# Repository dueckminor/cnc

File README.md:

# CNC-Mill

This is my first try to build a CNC-Mill

As a controller I use an ESP-32 with
[FluidNC](https://github.com/bdring/FluidNC)

I designed a PCB with the following features:
- 4 stepper motors (for the X1,X2,Y,Z axes)
- 1 spindle output (enable+pwm)
- 5 additional output pins
- 8 limit switches (5V powered), 2 for each axis
- 1 probe switch
- 3 additional input pins
- 1 SD-Card
- 1 I2C (for an OLED display)

This board gets connected using a 2x25 pin header to a connector-board
with many JST-XH connectors. This board contians also pull-up resistors
for each input switch (all inputs are active-low)

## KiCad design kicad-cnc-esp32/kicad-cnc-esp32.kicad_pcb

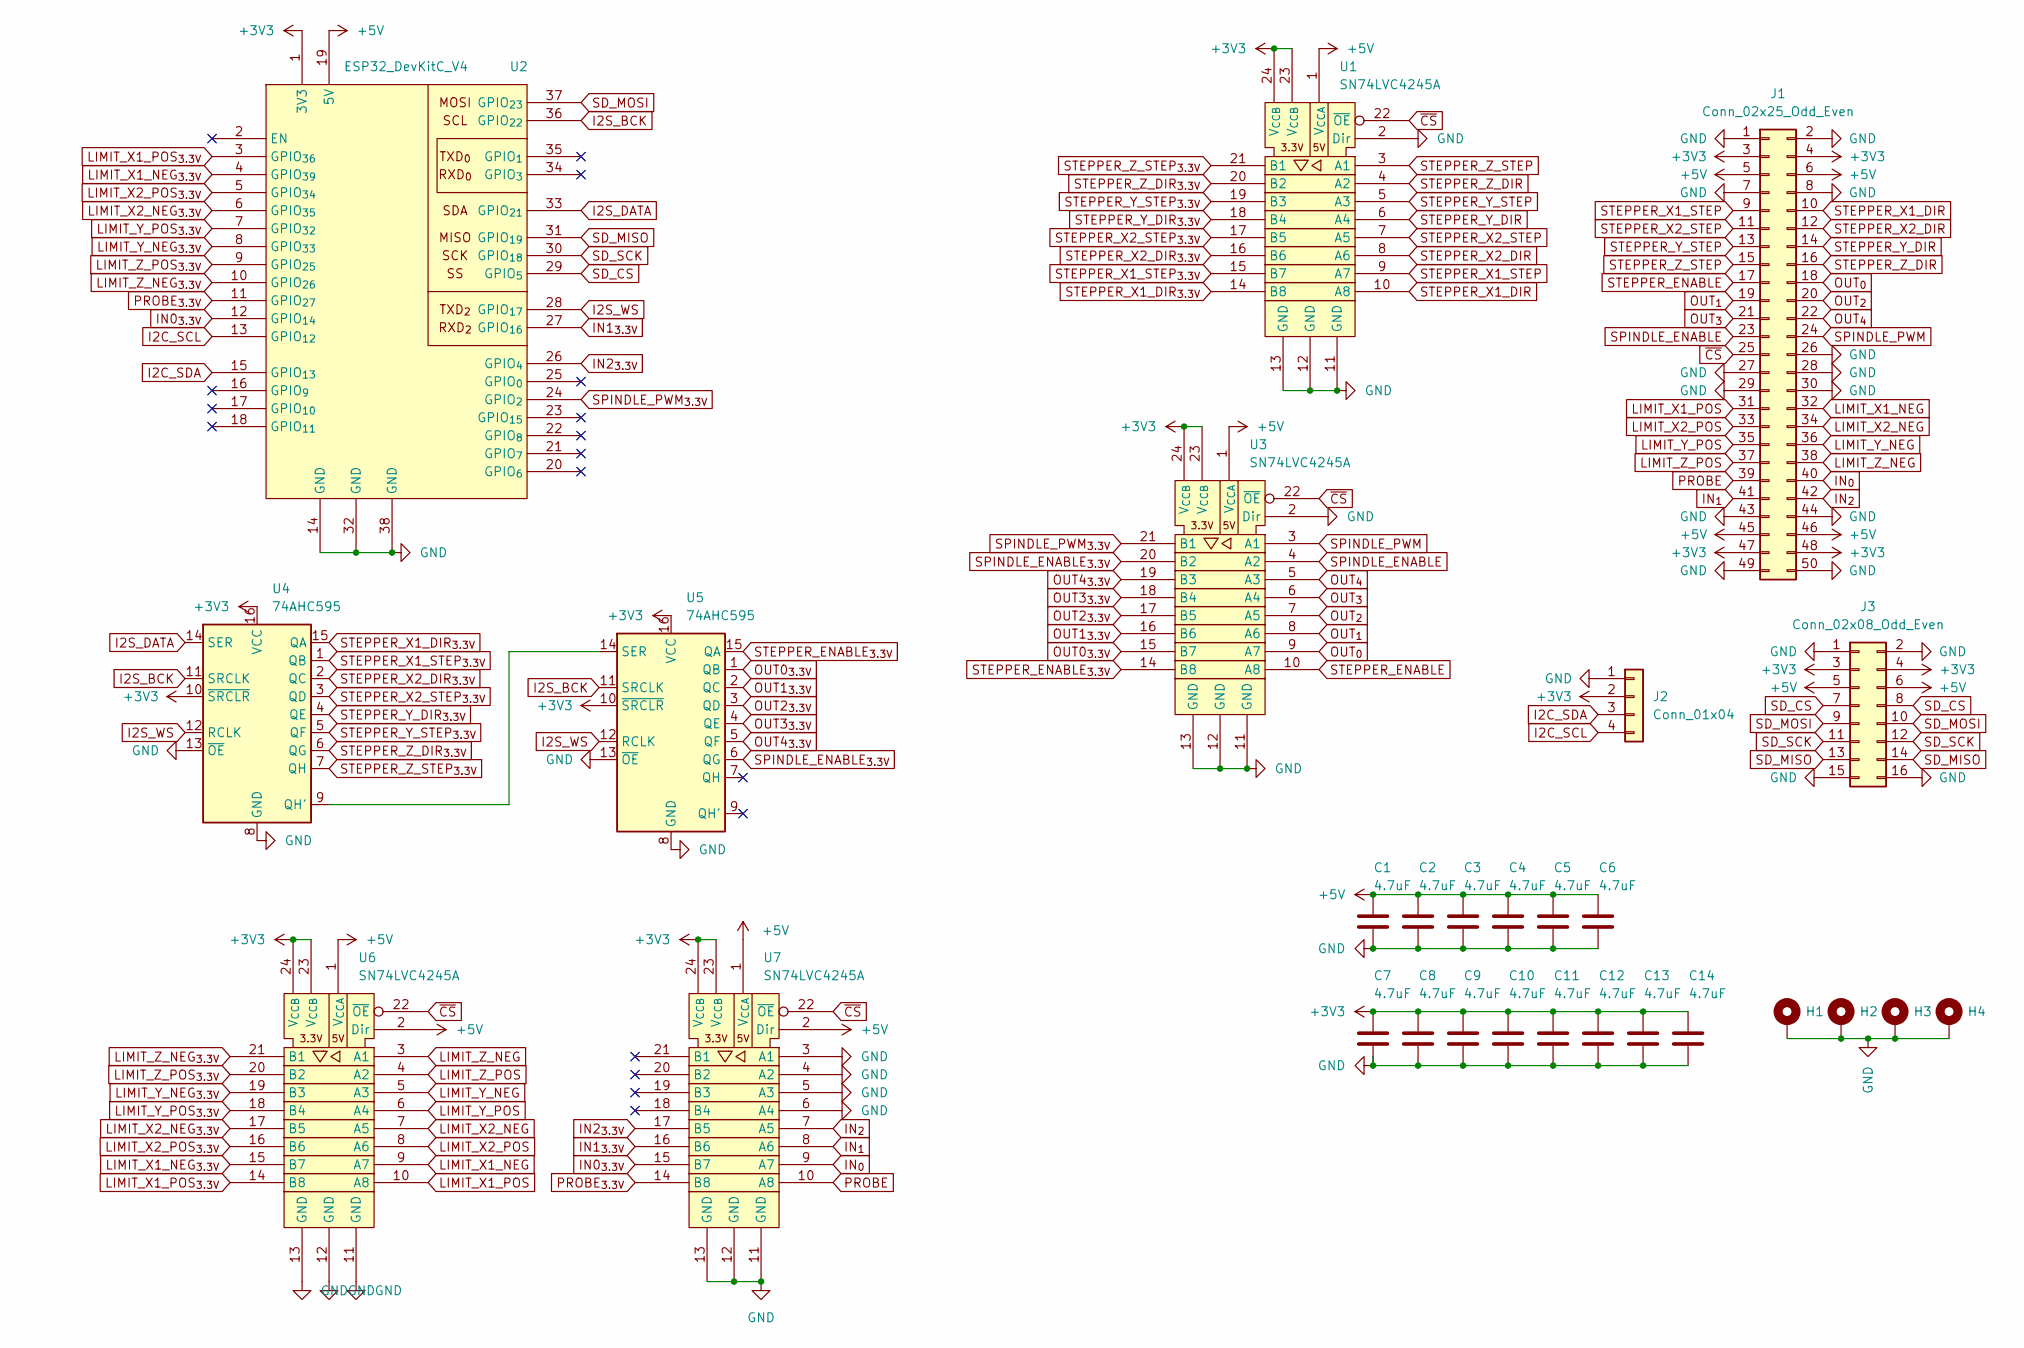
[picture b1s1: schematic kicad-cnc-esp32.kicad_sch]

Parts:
C1, C2, C3, C4, C5, C6, C7, C8, C9, C10, C11, C12, C13, C14: 4.7uF; C_0402_1005Metric; JLCPCB C23733
H1, H2, H3, H4: MountingHole_Pad; MountingHole_4.5mm_Pad_Via
J1: Conn_02x25_Odd_Even; PinHeader_2x25_P2.54mm_Horizontal
J2: Conn_01x04; JST_XH_B4B-XH-A_1x04_P2.50mm_Vertical
J3: Conn_02x08_Odd_Even; PinSocket_2x08_P2.54mm_Vertical
U1, U3, U6, U7: SN74LVC4245A; TSSOP-24_4.4x7.8mm_P0.65mm; JLCPCB C7859
U2: ESP32_DevKitC_V4
U4, U5: 74AHC595; SOIC-16_3.9x9.9mm_P1.27mm; JLCPCB C5947

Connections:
+3V3: C7.1, C8.1, C9.1, C10.1, C11.1, C12.1, C13.1, C14.1, J1.3, J1.4, J1.47, J1.48, J2.2, J3.3, J3.4, U1.23 (V_{CCB}), U1.24 (V_{CCB}), U2.1 (3V3), U3.23 (V_{CCB}), U3.24 (V_{CCB}), U4.10 (~SRCLR), U4.16 (VCC), U5.10 (~SRCLR), U5.16 (VCC), U6.23 (V_{CCB}), U6.24 (V_{CCB}), U7.23 (V_{CCB}), U7.24 (V_{CCB})
+5V: C1.1, C2.1, C3.1, C4.1, C5.1, C6.1, J1.5, J1.6, J1.45, J1.46, J3.5, J3.6, U1.1 (V_{CCA}), U2.19 (5V), U3.1 (V_{CCA}), U6.1 (V_{CCA}), U6.2 (Dir), U7.1 (V_{CCA}), U7.2 (Dir)
GND: C1.2, C2.2, C3.2, C4.2, C5.2, C6.2, C7.2, C8.2, C9.2, C10.2, C11.2, C12.2, C13.2, C14.2, H1.1, H2.1, H3.1, H4.1, J1.1, J1.2, J1.7, J1.8, J1.26, J1.27, J1.28, J1.29, J1.30, J1.43, J1.44, J1.49, J1.50, J2.1, J3.1, J3.2, J3.15, J3.16, U1.2 (Dir), U1.11 (GND), U1.12 (GND), U1.13 (GND), U2.14 (GND), U2.32 (GND), U2.38 (GND), U3.2 (Dir), U3.11 (GND), U3.12 (GND), U3.13 (GND), U4.8 (GND), U4.13 (~OE), U5.8 (GND), U5.13 (~OE), U6.11 (GND), U6.12 (GND), U6.13 (GND), U7.3 (A1), U7.4 (A2), U7.5 (A3), U7.6 (A4), U7.11 (GND), U7.12 (GND), U7.13 (GND)
I2C_SCL: J2.4, U2.13 (GPIO_{12})
I2C_SDA: J2.3, U2.15 (GPIO_{13})
I2S_BCK: U2.36 (GPIO_{22}), U4.11 (SRCLK), U5.11 (SRCLK)
I2S_DATA: U2.33 (GPIO_{21}), U4.14 (SER)
I2S_WS: U2.28 (GPIO_{17}), U4.12 (RCLK), U5.12 (RCLK)
IN0_{3.3V}: U2.12 (GPIO_{14}), U7.15 (B7)
IN1_{3.3V}: U2.27 (GPIO_{16}), U7.16 (B6)
IN2_{3.3V}: U2.26 (GPIO_{4}), U7.17 (B5)
IN_{0}: J1.40, U7.9 (A7)
IN_{1}: J1.41, U7.8 (A6)
IN_{2}: J1.42, U7.7 (A5)
LIMIT_X1_NEG: J1.32, U6.9 (A7)
LIMIT_X1_NEG_{3.3V}: U2.4 (GPIO_{39}), U6.15 (B7)
LIMIT_X1_POS: J1.31, U6.10 (A8)
LIMIT_X1_POS_{3.3V}: U2.3 (GPIO_{36}), U6.14 (B8)
LIMIT_X2_NEG: J1.34, U6.7 (A5)
LIMIT_X2_NEG_{3.3V}: U2.6 (GPIO_{35}), U6.17 (B5)
LIMIT_X2_POS: J1.33, U6.8 (A6)
LIMIT_X2_POS_{3.3V}: U2.5 (GPIO_{34}), U6.16 (B6)
LIMIT_Y_NEG: J1.36, U6.5 (A3)
LIMIT_Y_NEG_{3.3V}: U2.8 (GPIO_{33}), U6.19 (B3)
LIMIT_Y_POS: J1.35, U6.6 (A4)
LIMIT_Y_POS_{3.3V}: U2.7 (GPIO_{32}), U6.18 (B4)
LIMIT_Z_NEG: J1.38, U6.3 (A1)
LIMIT_Z_NEG_{3.3V}: U2.10 (GPIO_{26}), U6.21 (B1)
LIMIT_Z_POS: J1.37, U6.4 (A2)
LIMIT_Z_POS_{3.3V}: U2.9 (GPIO_{25}), U6.20 (B2)
unnamed: U4.9 (QH'), U5.14 (SER)
OUT0_{3.3V}: U3.15 (B7), U5.1 (QB)
OUT1_{3.3V}: U3.16 (B6), U5.2 (QC)
OUT2_{3.3V}: U3.17 (B5), U5.3 (QD)
OUT3_{3.3V}: U3.18 (B4), U5.4 (QE)
OUT4_{3.3V}: U3.19 (B3), U5.5 (QF)
OUT_{0}: J1.18, U3.9 (A7)
OUT_{1}: J1.19, U3.8 (A6)
OUT_{2}: J1.20, U3.7 (A5)
OUT_{3}: J1.21, U3.6 (A4)
OUT_{4}: J1.22, U3.5 (A3)
PROBE: J1.39, U7.10 (A8)
PROBE_{3.3V}: U2.11 (GPIO_{27}), U7.14 (B8)
SD_CS: J3.7, J3.8, U2.29 (GPIO_{5})
SD_MISO: J3.13, J3.14, U2.31 (GPIO_{19})
SD_MOSI: J3.9, J3.10, U2.37 (GPIO_{23})
SD_SCK: J3.11, J3.12, U2.30 (GPIO_{18})
SPINDLE_ENABLE: J1.23, U3.4 (A2)
SPINDLE_ENABLE_{3.3V}: U3.20 (B2), U5.6 (QG)
SPINDLE_PWM: J1.24, U3.3 (A1)
SPINDLE_PWM_{3.3V}: U2.24 (GPIO_{2}), U3.21 (B1)
STEPPER_ENABLE: J1.17, U3.10 (A8)
STEPPER_ENABLE_{3.3V}: U3.14 (B8), U5.15 (QA)
STEPPER_X1_DIR: J1.10, U1.10 (A8)
STEPPER_X1_DIR_{3.3V}: U1.14 (B8), U4.15 (QA)
STEPPER_X1_STEP: J1.9, U1.9 (A7)
STEPPER_X1_STEP_{3.3V}: U1.15 (B7), U4.1 (QB)
STEPPER_X2_DIR: J1.12, U1.8 (A6)
STEPPER_X2_DIR_{3.3V}: U1.16 (B6), U4.2 (QC)
STEPPER_X2_STEP: J1.11, U1.7 (A5)
STEPPER_X2_STEP_{3.3V}: U1.17 (B5), U4.3 (QD)
STEPPER_Y_DIR: J1.14, U1.6 (A4)
STEPPER_Y_DIR_{3.3V}: U1.18 (B4), U4.4 (QE)
STEPPER_Y_STEP: J1.13, U1.5 (A3)
STEPPER_Y_STEP_{3.3V}: U1.19 (B3), U4.5 (QF)
STEPPER_Z_DIR: J1.16, U1.4 (A2)
STEPPER_Z_DIR_{3.3V}: U1.20 (B2), U4.6 (QG)
STEPPER_Z_STEP: J1.15, U1.3 (A1)
STEPPER_Z_STEP_{3.3V}: U1.21 (B1), U4.7 (QH)
~CS: J1.25, U1.22 (~OE), U3.22 (~OE), U6.22 (~OE), U7.22 (~OE)

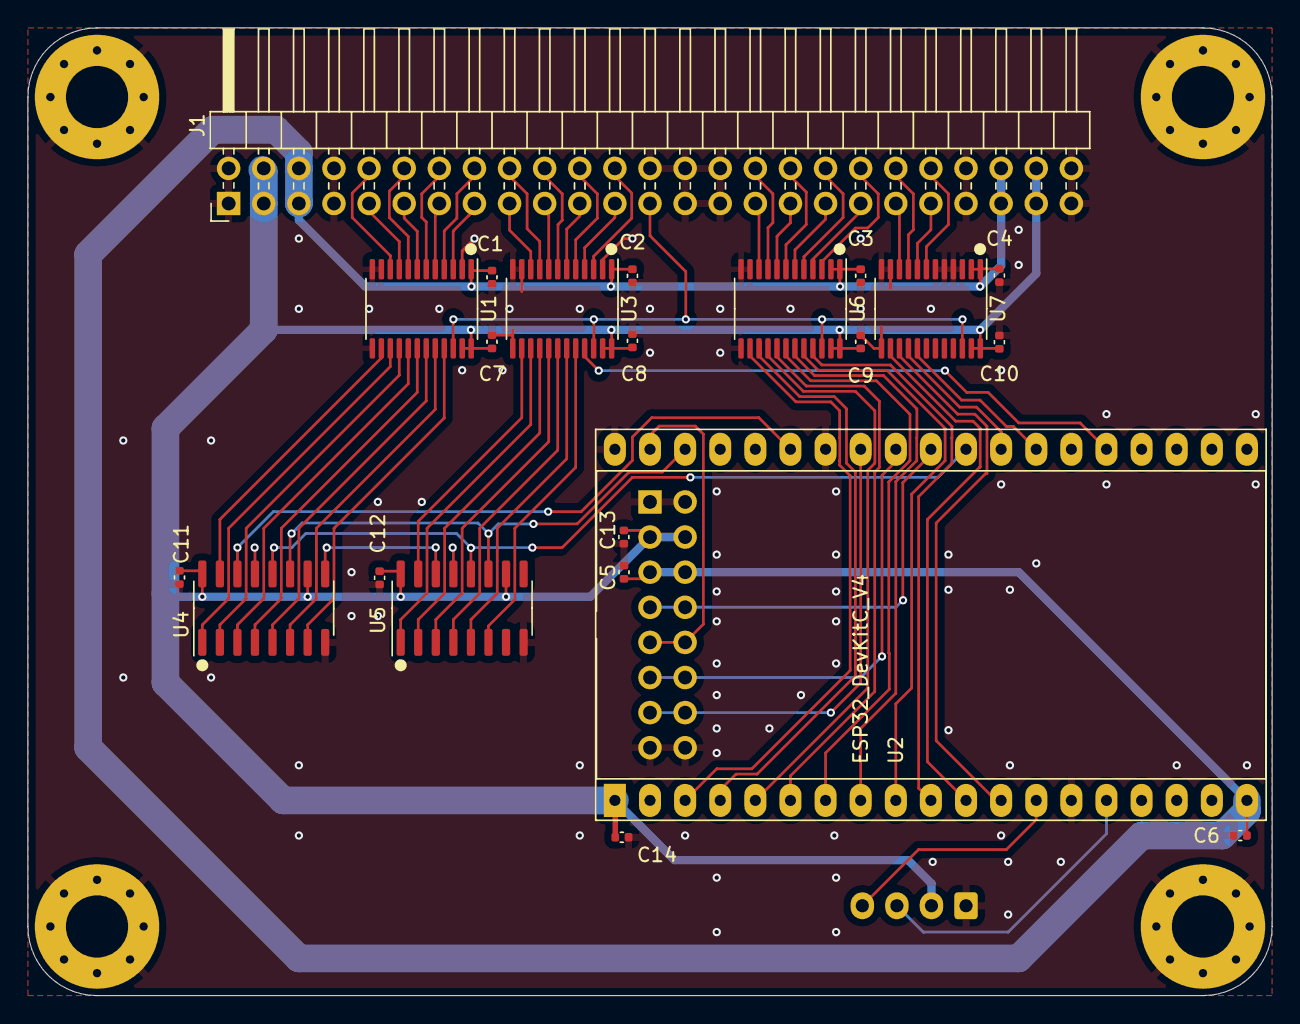
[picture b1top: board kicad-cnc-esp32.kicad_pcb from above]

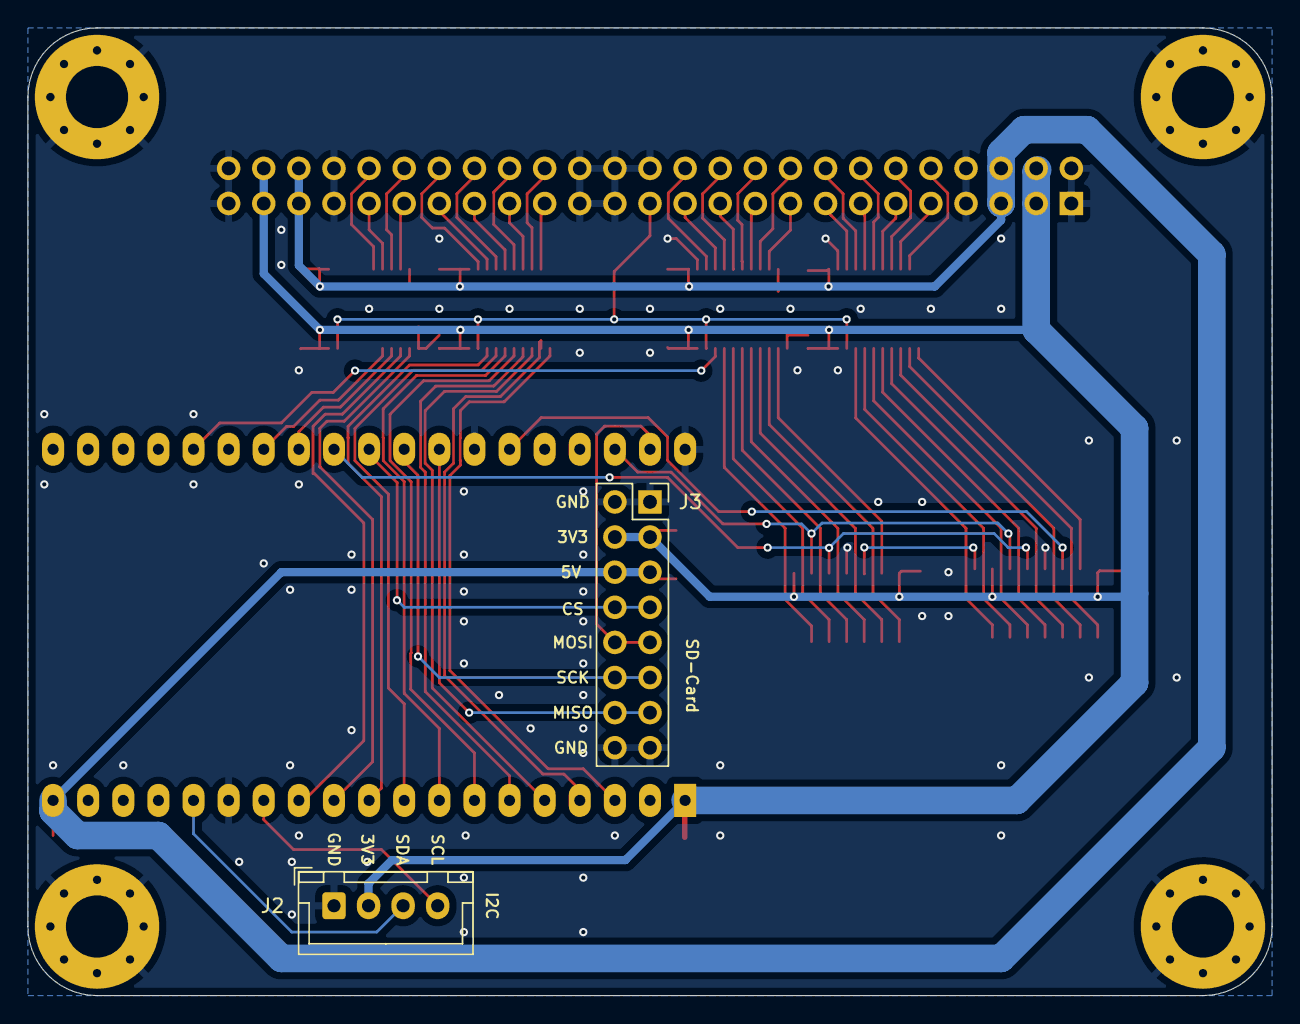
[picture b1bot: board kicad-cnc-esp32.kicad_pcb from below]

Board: 2 copper layers, 90.0 x 70.0 mm, 28 parts (2 on the bottom side), 70 nets.

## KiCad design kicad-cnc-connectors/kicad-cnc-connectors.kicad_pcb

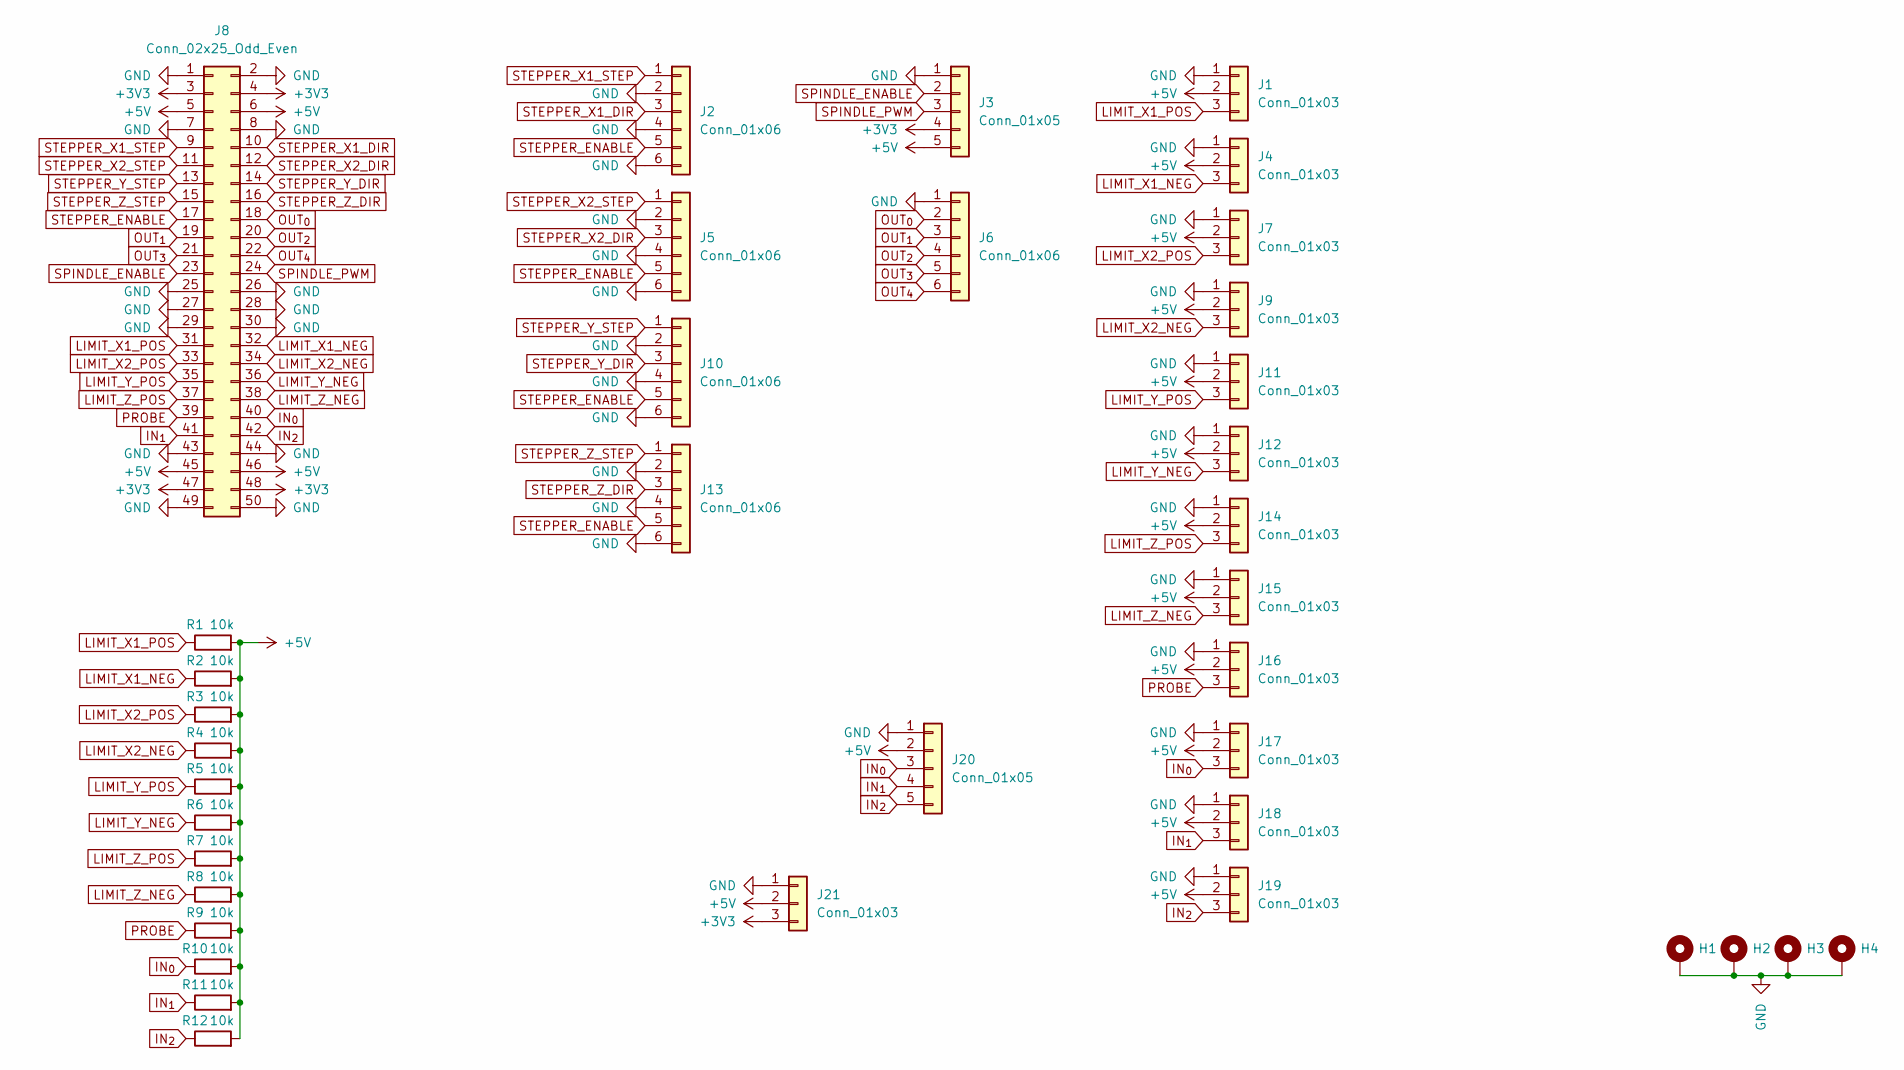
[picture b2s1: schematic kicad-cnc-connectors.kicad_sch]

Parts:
H1, H2, H3, H4: MountingHole_Pad; MountingHole_4.5mm_Pad_Via
J1, J4, J7, J9, J11, J12, J14, J15, J16, J17, J18, J19, J21: Conn_01x03; JST_XH_B3B-XH-A_1x03_P2.50mm_Vertical
J2, J5, J6, J10, J13: Conn_01x06; JST_XH_B6B-XH-A_1x06_P2.50mm_Vertical
J3, J20: Conn_01x05; JST_XH_B5B-XH-A_1x05_P2.50mm_Vertical
J8: Conn_02x25_Odd_Even; PinSocket_2x25_P2.54mm_Vertical
R1, R2, R3, R4, R5, R6, R7, R8, R9, R10, R11, R12: 10k; R_0402_1005Metric

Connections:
+3V3: J3.4, J8.3, J8.4, J8.47, J8.48, J21.3
+5V: J1.2, J3.5, J4.2, J7.2, J8.5, J8.6, J8.45, J8.46, J9.2, J11.2, J12.2, J14.2, J15.2, J16.2, J17.2, J18.2, J19.2, J20.2, J21.2, R1.2, R2.2, R3.2, R4.2, R5.2, R6.2, R7.2, R8.2, R9.2, R10.2, R11.2, R12.2
GND: H1.1, H2.1, H3.1, H4.1, J1.1, J2.2, J2.4, J2.6, J3.1, J4.1, J5.2, J5.4, J5.6, J6.1, J7.1, J8.1, J8.2, J8.7, J8.8, J8.25, J8.26, J8.27, J8.28, J8.29, J8.30, J8.43, J8.44, J8.49, J8.50, J9.1, J10.2, J10.4, J10.6, J11.1, J12.1, J13.2, J13.4, J13.6, J14.1, J15.1, J16.1, J17.1, J18.1, J19.1, J20.1, J21.1
IN_{0}: J8.40, J17.3, J20.3, R10.1
IN_{1}: J8.41, J18.3, J20.4, R11.1
IN_{2}: J8.42, J19.3, J20.5, R12.1
LIMIT_X1_NEG: J4.3, J8.32, R2.1
LIMIT_X1_POS: J1.3, J8.31, R1.1
LIMIT_X2_NEG: J8.34, J9.3, R4.1
LIMIT_X2_POS: J7.3, J8.33, R3.1
LIMIT_Y_NEG: J8.36, J12.3, R6.1
LIMIT_Y_POS: J8.35, J11.3, R5.1
LIMIT_Z_NEG: J8.38, J15.3, R8.1
LIMIT_Z_POS: J8.37, J14.3, R7.1
OUT_{0}: J6.2, J8.18
OUT_{1}: J6.3, J8.19
OUT_{2}: J6.4, J8.20
OUT_{3}: J6.5, J8.21
OUT_{4}: J6.6, J8.22
PROBE: J8.39, J16.3, R9.1
SPINDLE_ENABLE: J3.2, J8.23
SPINDLE_PWM: J3.3, J8.24
STEPPER_ENABLE: J2.5, J5.5, J8.17, J10.5, J13.5
STEPPER_X1_DIR: J2.3, J8.10
STEPPER_X1_STEP: J2.1, J8.9
STEPPER_X2_DIR: J5.3, J8.12
STEPPER_X2_STEP: J5.1, J8.11
STEPPER_Y_DIR: J8.14, J10.3
STEPPER_Y_STEP: J8.13, J10.1
STEPPER_Z_DIR: J8.16, J13.3
STEPPER_Z_STEP: J8.15, J13.1

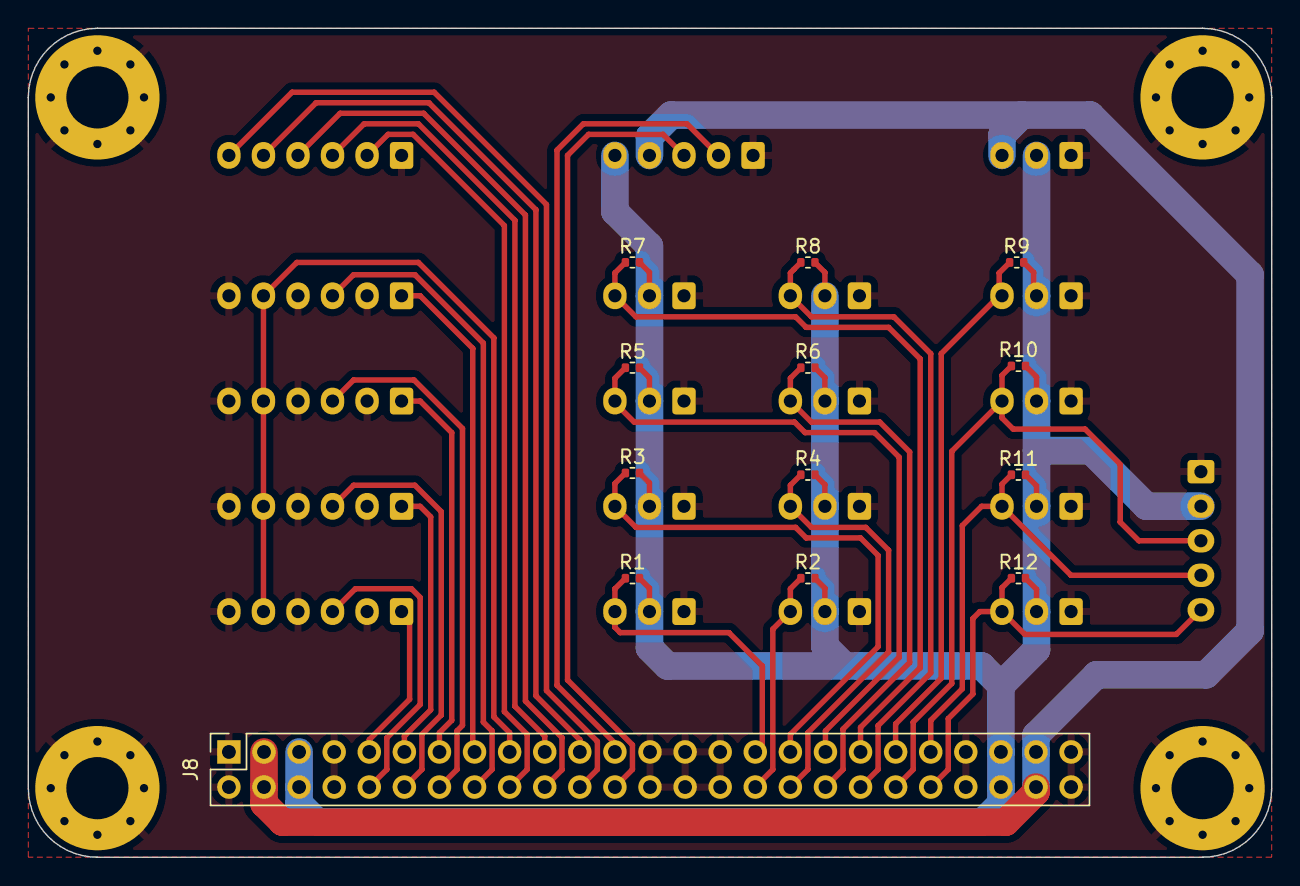
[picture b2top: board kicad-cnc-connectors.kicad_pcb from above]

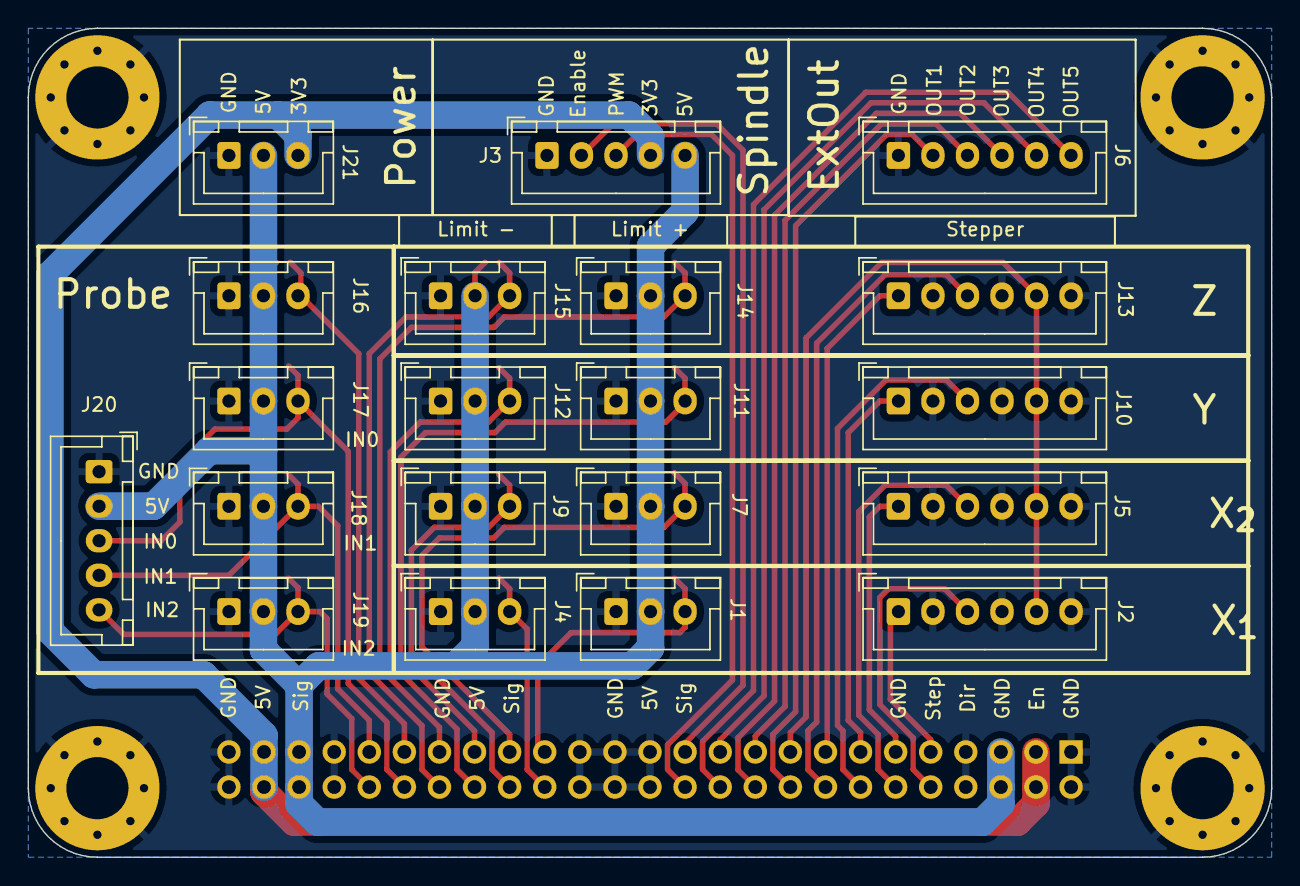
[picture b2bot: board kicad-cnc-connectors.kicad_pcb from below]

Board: 2 copper layers, 90.0 x 60.0 mm, 37 parts (20 on the bottom side), 31 nets.

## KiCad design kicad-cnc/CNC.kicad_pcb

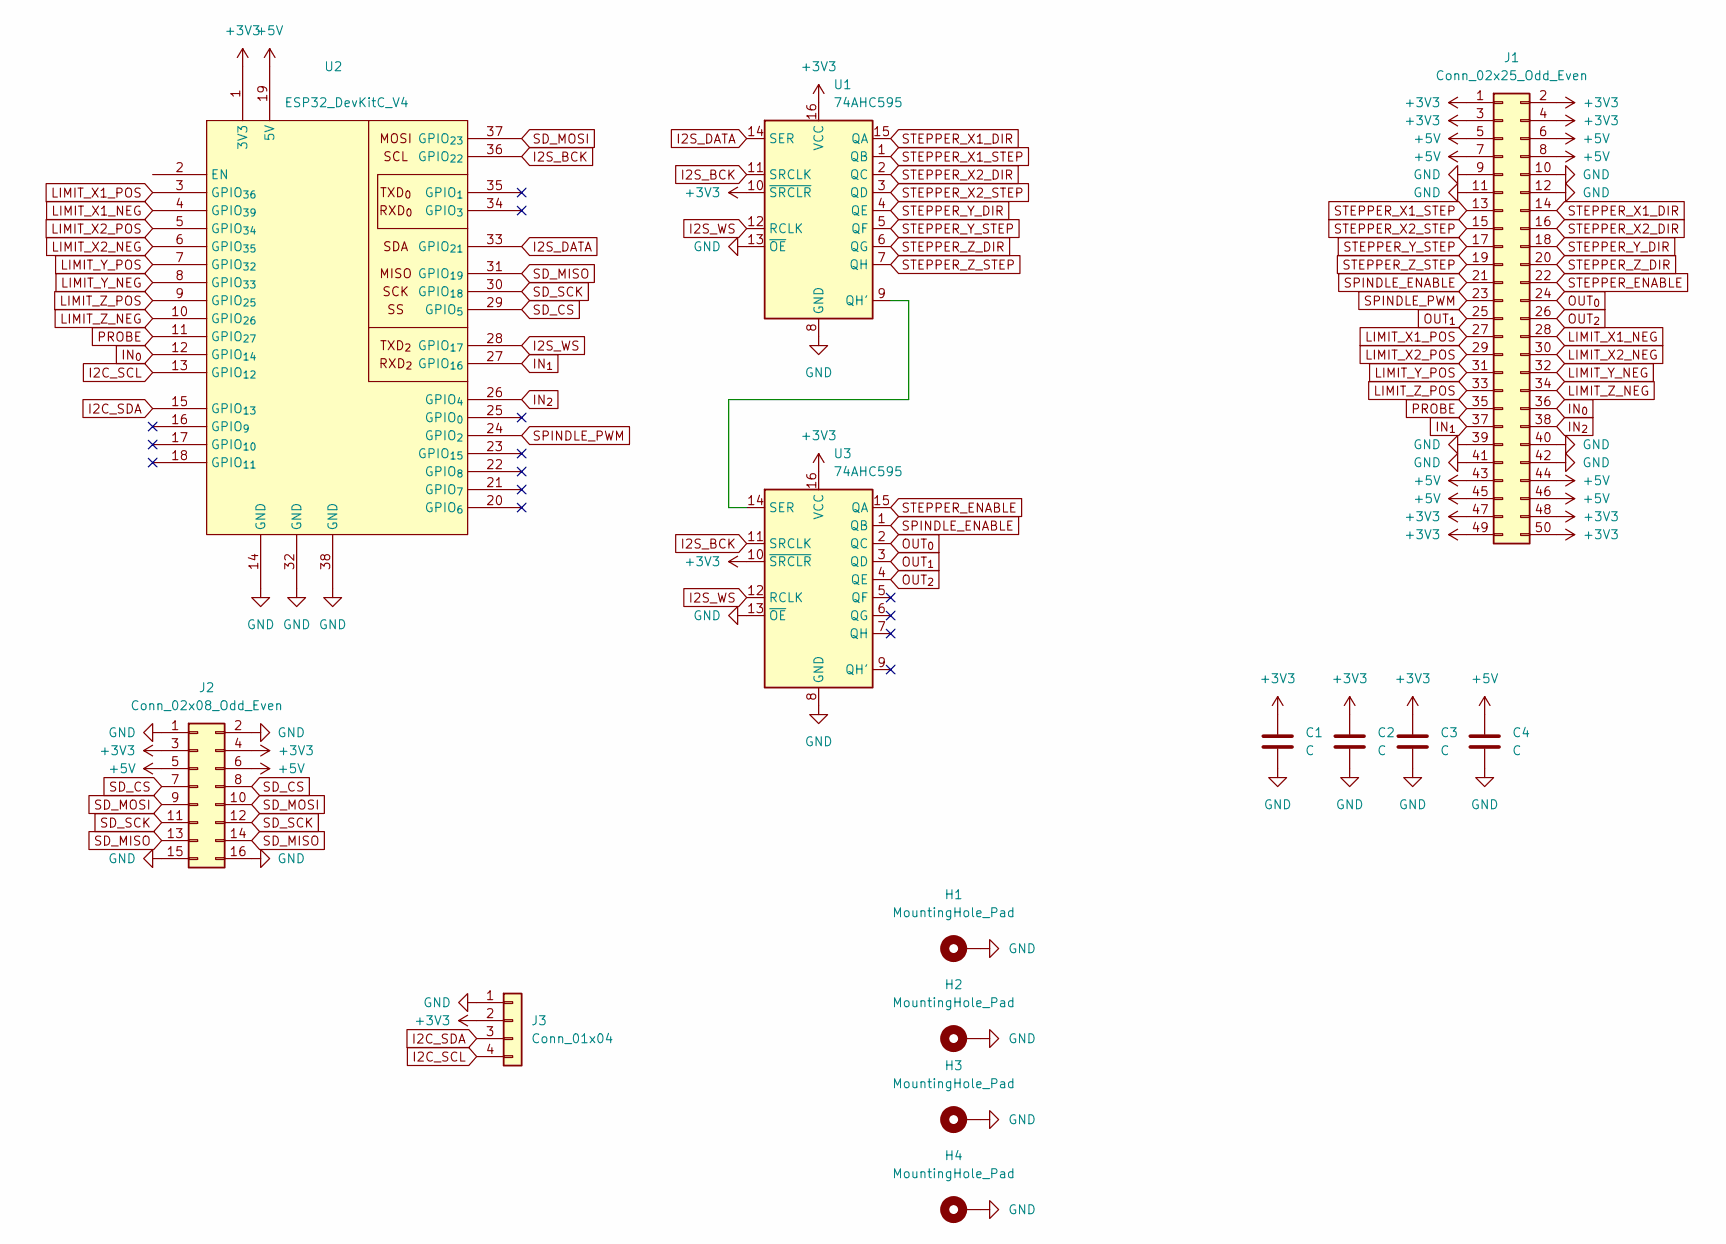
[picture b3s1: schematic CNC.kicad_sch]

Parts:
C1, C2, C3, C4: C; C_0402_1005Metric
H1, H2, H3, H4: MountingHole_Pad; MountingHole_4.5mm_Pad_Via
J1: Conn_02x25_Odd_Even; PinHeader_2x25_P2.54mm_Horizontal
J2: Conn_02x08_Odd_Even; PinSocket_2x08_P2.54mm_Vertical
J3: Conn_01x04; JST_XH_B4B-XH-A_1x04_P2.50mm_Vertical
U1, U3: 74AHC595; SOIC-16_3.9x9.9mm_P1.27mm
U2: ESP32_DevKitC_V4

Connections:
+3V3: C1.1, C2.1, C3.1, J1.1, J1.2, J1.3, J1.4, J1.47, J1.48, J1.49, J1.50, J2.3, J2.4, J3.2, U1.10 (~SRCLR), U1.16 (VCC), U2.1 (3V3), U3.10 (~SRCLR), U3.16 (VCC)
+5V: C4.1, J1.5, J1.6, J1.7, J1.8, J1.43, J1.44, J1.45, J1.46, J2.5, J2.6, U2.19 (5V)
GND: C1.2, C2.2, C3.2, C4.2, H1.1, H2.1, H3.1, H4.1, J1.9, J1.10, J1.11, J1.12, J1.39, J1.40, J1.41, J1.42, J2.1, J2.2, J2.15, J2.16, J3.1, U1.8 (GND), U1.13 (~OE), U2.14 (GND), U2.32 (GND), U2.38 (GND), U3.8 (GND), U3.13 (~OE)
I2C_SCL: J3.4, U2.13 (GPIO_{12})
I2C_SDA: J3.3, U2.15 (GPIO_{13})
I2S_BCK: U1.11 (SRCLK), U2.36 (GPIO_{22}), U3.11 (SRCLK)
I2S_DATA: U1.14 (SER), U2.33 (GPIO_{21})
I2S_WS: U1.12 (RCLK), U2.28 (GPIO_{17}), U3.12 (RCLK)
IN_{0}: J1.36, U2.12 (GPIO_{14})
IN_{1}: J1.37, U2.27 (GPIO_{16})
IN_{2}: J1.38, U2.26 (GPIO_{4})
LIMIT_X1_NEG: J1.28, U2.4 (GPIO_{39})
LIMIT_X1_POS: J1.27, U2.3 (GPIO_{36})
LIMIT_X2_NEG: J1.30, U2.6 (GPIO_{35})
LIMIT_X2_POS: J1.29, U2.5 (GPIO_{34})
LIMIT_Y_NEG: J1.32, U2.8 (GPIO_{33})
LIMIT_Y_POS: J1.31, U2.7 (GPIO_{32})
LIMIT_Z_NEG: J1.34, U2.10 (GPIO_{26})
LIMIT_Z_POS: J1.33, U2.9 (GPIO_{25})
unnamed: U1.9 (QH'), U3.14 (SER)
OUT_{0}: J1.24, U3.2 (QC)
OUT_{1}: J1.25, U3.3 (QD)
OUT_{2}: J1.26, U3.4 (QE)
PROBE: J1.35, U2.11 (GPIO_{27})
SD_CS: J2.7, J2.8, U2.29 (GPIO_{5})
SD_MISO: J2.13, J2.14, U2.31 (GPIO_{19})
SD_MOSI: J2.9, J2.10, U2.37 (GPIO_{23})
SD_SCK: J2.11, J2.12, U2.30 (GPIO_{18})
SPINDLE_ENABLE: J1.21, U3.1 (QB)
SPINDLE_PWM: J1.23, U2.24 (GPIO_{2})
STEPPER_ENABLE: J1.22, U3.15 (QA)
STEPPER_X1_DIR: J1.14, U1.15 (QA)
STEPPER_X1_STEP: J1.13, U1.1 (QB)
STEPPER_X2_DIR: J1.16, U1.2 (QC)
STEPPER_X2_STEP: J1.15, U1.3 (QD)
STEPPER_Y_DIR: J1.18, U1.4 (QE)
STEPPER_Y_STEP: J1.17, U1.5 (QF)
STEPPER_Z_DIR: J1.20, U1.6 (QG)
STEPPER_Z_STEP: J1.19, U1.7 (QH)

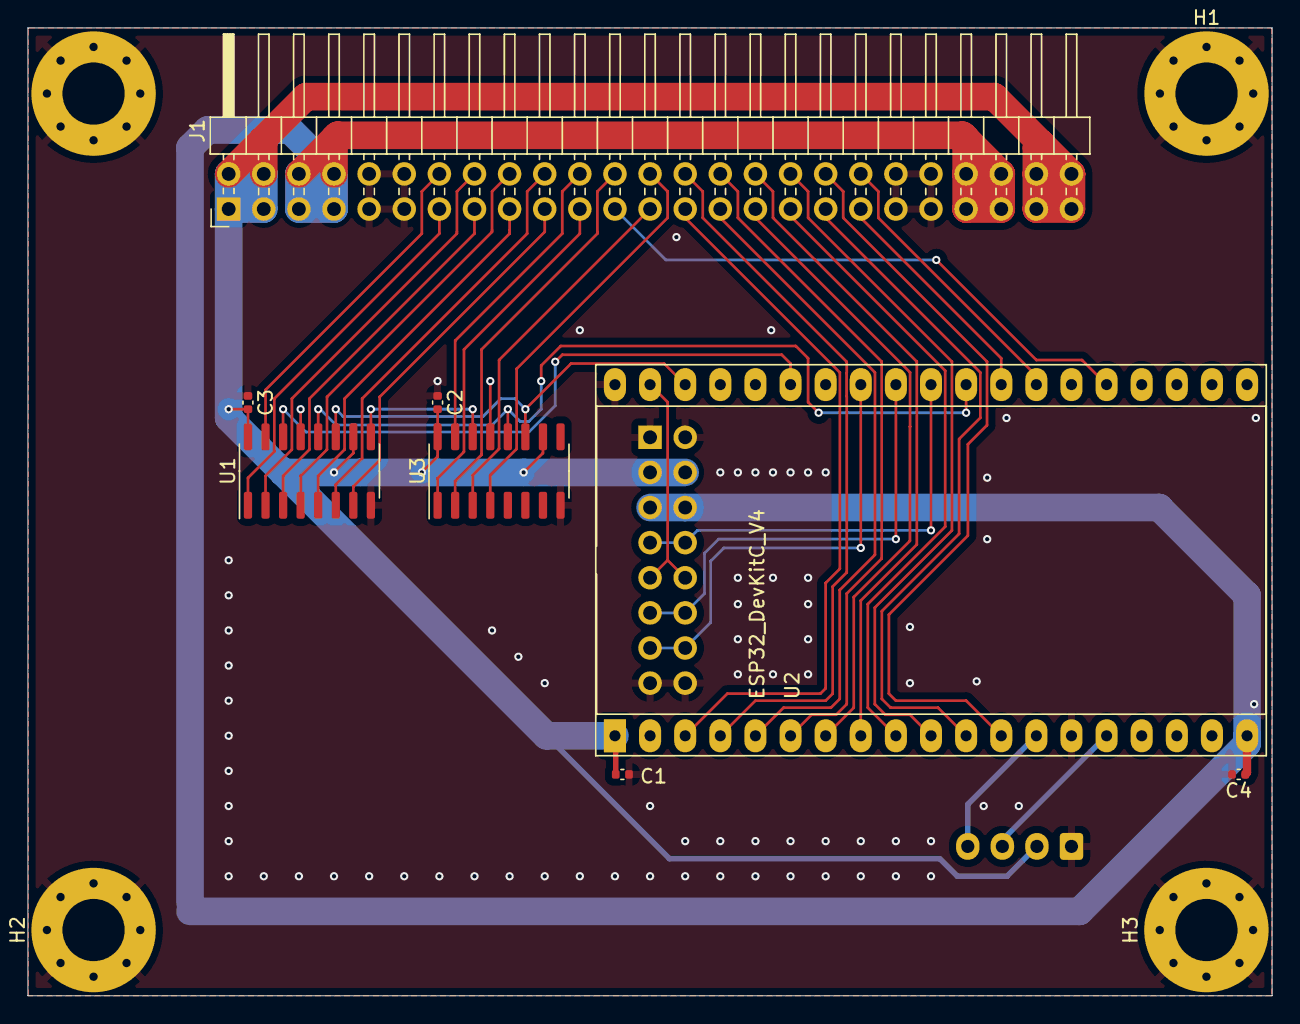
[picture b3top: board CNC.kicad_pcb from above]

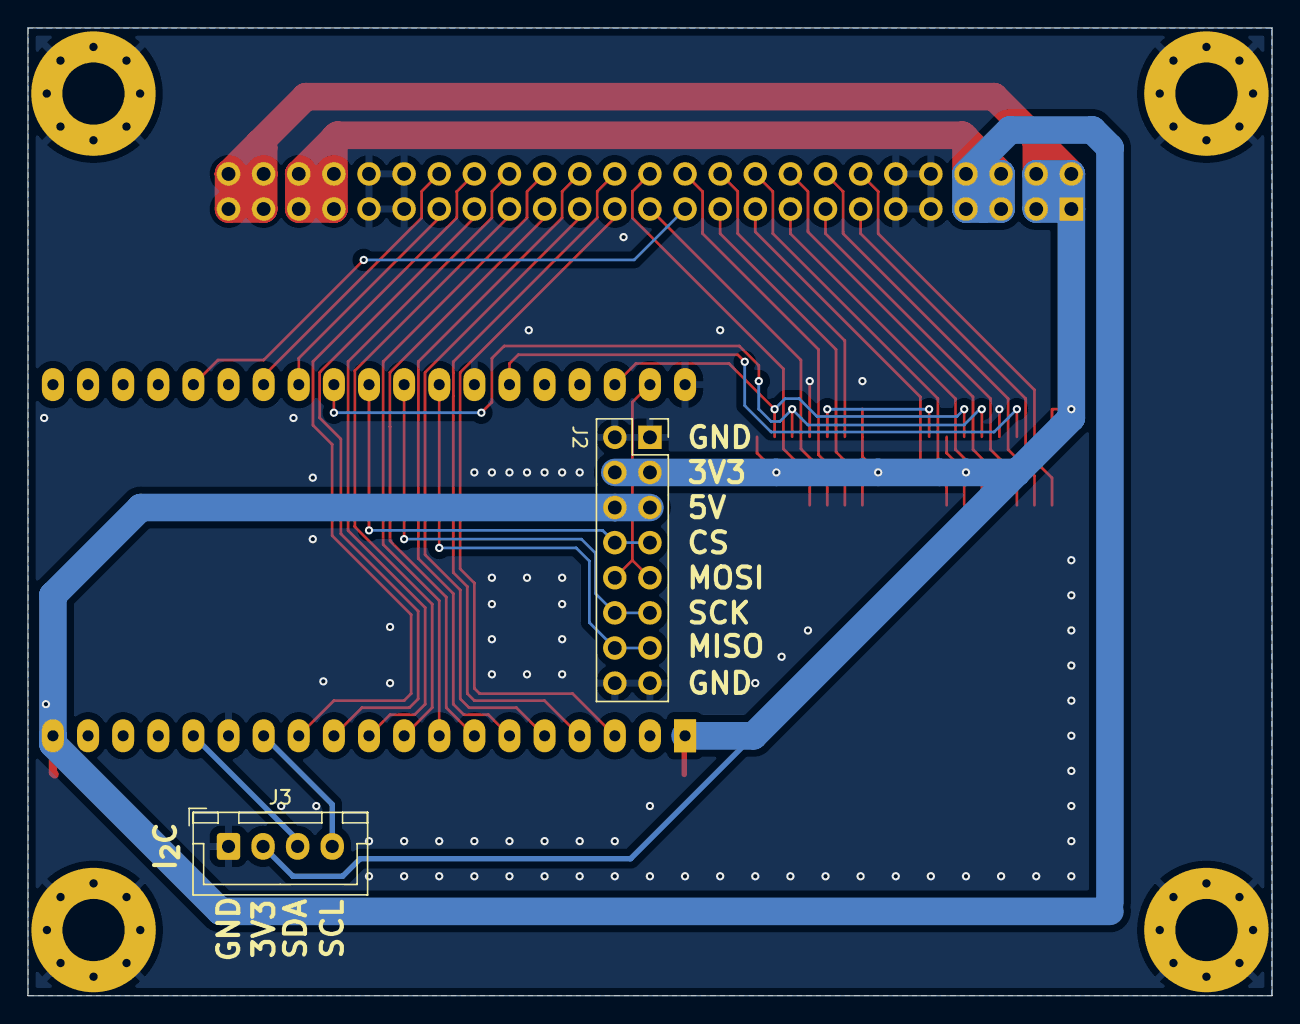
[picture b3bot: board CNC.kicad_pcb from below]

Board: 4 copper layers, 90.0 x 70.0 mm, 14 parts (2 on the bottom side), 39 nets.
